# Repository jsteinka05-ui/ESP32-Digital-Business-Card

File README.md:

# ESP32 Digital Business Card

A standalone digital business card built around a **Seeed Studio XIAO ESP32-C3** and a **3.5-inch ILI9488 SPI TFT display**. This repository documents its hardware and a firmware rewrite in **C using ESP-IDF**.

The device is designed to display personal contact information and a LinkedIn QR code, with a single button for slide navigation, display recovery, and wake-up.

[Watch the device demonstration](docs/media/device-demo.mp4) — slide transitions, LCD power switching, and display recovery.

## Project Status

The custom PCB assembly, wiring, printed enclosure, and C firmware rewrite are complete. The ESP-IDF v6.1 firmware supports debounced button input, embedded slides, animated navigation, LCD recovery, and five-minute inactivity sleep with button wake.

Functional hardware checks and a clean-checkout build are complete. Recorded results include five startup draws at 238 ms each and twenty transitions averaging 2,604.75 ms, with unchanged sampled free heap. See the [validation record](docs/testing.md) for methods and limits. Current consumption and physical wake latency are outside this release's measurement scope.

Hardware design files and printable enclosure models are available under [hardware/](hardware/README.md).

## Features

- Business-card and LinkedIn QR-code slides.
- Standalone operation with images embedded in firmware; no network connection or SD card required.
- Animated transitions controlled by a physical button.
- Long-press recovery after the LCD is power-cycled independently of the microcontroller.

- Low-power idle after five minutes without button input.
- Button wake-up that restores the current slide without advancing it.

The current backlight is powered directly from the display supply. Automatic backlight shutdown would require a hardware change. Wi-Fi and Bluetooth Low Energy are future expansion options.

## Hardware and Design Choices

| Part | Purpose |
|---|---|
| Seeed Studio XIAO ESP32-C3 | Compact controller with flash storage, SPI, and room for wireless expansion |
| 3.5-inch ILI9488 SPI TFT | Color contact-information and QR-code display |
| Momentary pushbutton | Navigation, display recovery, and wake-up |
| LCD power switch | Controls LCD power independently of the microcontroller |

The ESP32-C3 can be considered overkill for displaying two images and reading a button. I chose it to leave room for future Wi-Fi and Bluetooth Low Energy functionality without replacing the controller.

Embedded images keep the initial storage design simple, while SPI limits the display wiring. The tradeoffs include flash usage, display-update bandwidth, and the need to rebuild firmware when artwork changes.

See the [design document](docs/design.md) for component rationale, wiring, memory calculations, and power-management considerations.

## Intended Controls

The firmware rewrite targets the following controls, including sleep and wake behavior:

| Input or condition | Intended behavior |
|---|---|
| Short press: less than 900 ms | Advance to the next slide upon release |
| Long press: at least 900 ms | Reinitialize the LCD and redraw the current slide upon release |
| Five minutes without button input | Enter a low-power idle state |
| Button press while idle | Wake and restore the current slide; consume the gesture without navigation |

The LCD switch leaves the ESP32-C3 running. Display recovery is needed because restoring LCD power does not automatically repeat the panel initialization sequence.

Button-only wake-up assumes the LCD supply switch remains on. If the LCD is manually switched off, restore its power before waking the device or requesting display recovery.

## Repository Layout

```text
firmware/                 ESP-IDF application and build configuration
    main/                 Application logic
    components/ili9488/   Display driver
    images/               Source artwork and display assets
    tools/                Image conversion utilities
hardware/                 Hardware documentation
    schematic/            KiCad project, PCB, schematic, and local libraries
    manufacturing/        Versioned Gerber and drill packages
    enclosure/            Printable STL models and enclosure notes
docs/                     Design decisions and testing documentation
.github/workflows/        Future automated build checks
```

## Development Setup

The intended development environment is:

- VS Code with ESP-IDF extension.
- ESP-IDF with the ESP32-C3 target and its toolchain.
- A USB data connection to the XIAO ESP32-C3.
- Python with Pillow for artwork conversion; the saved RGB assets allow firmware builds without Pillow.

Firmware development takes place under `firmware/`. The application includes debounced input, streamed image drawing, and slide navigation. The [progress log](docs/progress.md) distinguishes implemented features from verified hardware behavior.

## Roadmap

- [x] Establish repository structure and ignore rules.
- [x] Document the initial design.
- [x] Complete prototype wiring, custom PCB assembly, and printed enclosure.
- [x] Organize KiCad files, manufacturing exports, and enclosure models.
- [x] Implement startup logging and debounced button input.
- [x] Initialize the display and verify drawing, colors, and orientation.
- [x] Display embedded slides and implement navigation.
- [x] Add LCD recovery and animated transitions.
- [x] Implement inactivity sleep and button wake-up.
- [x] Verify sleep/wake on hardware.
- [x] Publish build instructions, test results, and a device demonstration.

## Documentation

- [Firmware rewrite design](docs/design.md): architecture, hardware selection, interaction rules, and validation plan.
- [Firmware validation](docs/testing.md): build checks, simulated button tests, and hardware results.
- [Firmware development plan](docs/firmware-plan.md): implementation stages and completion criteria.
- [Hardware](hardware/README.md): KiCad project, parts inventory, and manufacturing revisions.
- [Enclosure](hardware/enclosure/README.md): top case, bottom case, and button models.
- [Progress and commit log](docs/progress.md): milestones, checks, and commit references.

## License

Third-party library sources and licensing are listed in the [library documentation](hardware/schematic/libraries/README.md), with the upstream license included alongside its files.

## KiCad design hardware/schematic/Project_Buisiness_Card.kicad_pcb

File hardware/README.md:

# Hardware

The digital business card uses a custom PCB and a three-part printed enclosure. PCB assembly, wiring, and the physical prototype are complete.

## Directory Layout

```text
schematic/
    Project_Buisiness_Card.kicad_pro  KiCad project
    Project_Buisiness_Card.kicad_sch  Circuit schematic
    Project_Buisiness_Card.kicad_pcb  PCB layout
    fp-lib-table                    Footprint libraries
    sym-lib-table                   Symbol libraries
    Library.pretty/                 Custom footprint library
    libraries/                      XIAO symbols and footprints
manufacturing/
    Buisiness_Card_Gerbers_1.2.zip
    Buisiness_Card_Gerbers_1.3.zip
    Project_Buisiness_Gerbers_1.4.zip
enclosure/
    Top_Case.stl
    Bottom_Case.stl
    Button (1).stl
```

The schematic, PCB, and project settings share a directory and base name so KiCad can associate them as one project.

## KiCad Project

Open [Project_Buisiness_Card.kicad_pro](schematic/Project_Buisiness_Card.kicad_pro) in KiCad 9.0. The XIAO libraries are stored locally and use project-relative paths.

The PCB uses a custom through-hole XIAO footprint. The original surface-mount footprint is available under a separate library name. The active assignment uses the through-hole version.

[Library documentation](schematic/libraries/README.md) describes the footprint variants, project assignments, and upstream sources.

## Fabricated PCB

Bare revision 1.4 PCB before component installation. The component side shows the XIAO footprint, display header, passive-component positions, and button and power-switch connections.

| Component side | Reverse side |
|---|---|
|  |  |

## Manufacturing Files

Version **1.4** is the current hardware revision. Versions 1.2 and 1.3 are retained as earlier exports. Each archive contains Gerber layers and plated/non-plated drill files.

## Enclosure

The enclosure consists of a [top case](enclosure/Top_Case.stl), [bottom case](enclosure/Bottom_Case.stl), and [button](<enclosure/Button (1).stl>).

See the [enclosure documentation](enclosure/README.md) for the printable models.

## Components

| Component | Quantity | Function |
|---|---:|---|
| Seeed Studio XIAO ESP32-C3 | 1 | Display control and button processing |
| 3.5-inch ILI9488 SPI TFT | 1 | Contact-information and QR-code display |
| SPST slide switch | 1 | LCD power control |
| Momentary pushbutton | 1 | Slide navigation and display recovery |
| 1 × 14 header, 2.54 mm pitch | 1 | LCD connection |

## Schematic Values and Footprint Assignments

These entries describe the KiCad design. Switch model names identify the assigned footprints.

| Reference | Schematic value | Footprint |
|---|---|---|
| U1 | XIAO ESP32C3 | Project-specific through-hole XIAO footprint |
| SW1 | SW_SPST | Wuerth WS-SLTV slide-switch footprint |
| SW2 | SW_Push | APEM MJTP1243 pushbutton footprint |
| J_LCD1 | Conn_01x14 | 1 × 14 pin header, 2.54 mm pitch |
| J_BAT1 | Two-pin connector | — |
| C1, C3 | 0.1 µF | Radial capacitor, 5 mm lead spacing |
| C2, C4 | 10 µF | Radial capacitor, 5 mm lead spacing |
| R4, R6 | `46` | Axial resistor, 7.62 mm lead spacing |

The [design specification](../docs/design.md#existing-prototype-wiring) contains the GPIO mapping and LCD power behavior.

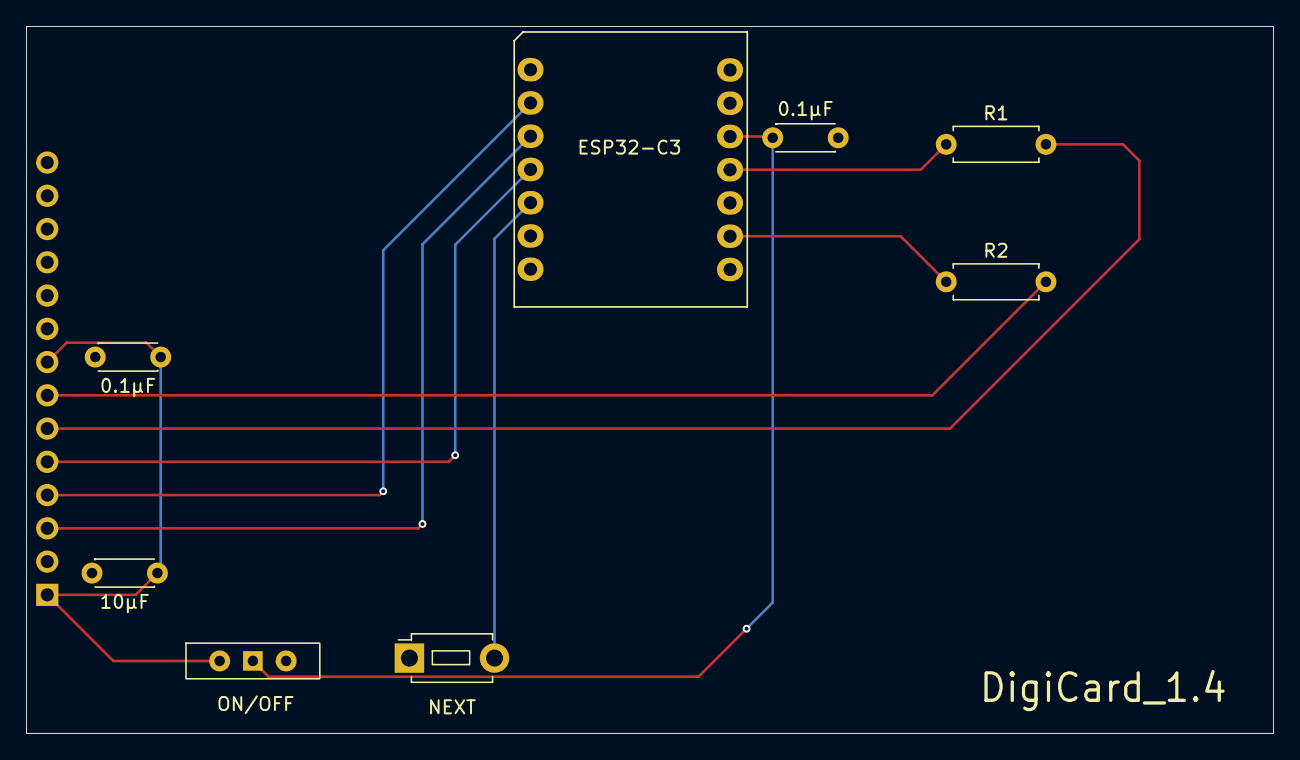
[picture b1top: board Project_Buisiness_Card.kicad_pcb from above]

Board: 2 copper layers, 95.2 x 54.0 mm, 9 parts (1 on the bottom side), 11 nets.

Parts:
0.1μF, 0.1μF#2: 0.1u; C_Disc_D4.3mm_W1.9mm_P5.00mm
10μF: 10u; C_Disc_D4.3mm_W1.9mm_P5.00mm
J_LCD1: Conn_01x14; PinHeader_1x14_P2.54mm_Vertical
NEXT: SW_Push; SW_PUSH_1P1T_6x3.5mm_H4.3_APEM_MJTP1243
R1, R2: 46; R_Axial_DIN0207_L6.3mm_D2.5mm_P7.62mm_Horizontal
SW1: SW_SPST; SW_Slide-03_Wuerth-WS-SLTV_10x2.5x6.4_P2.54mm
U1: XIAO ESP32C3; MOUDLE14P-SMD-2.54-21X17.8MM

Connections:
GND: 0.1μF.2, 0.1μF#2.2, 10μF.2, J_LCD1.2, NEXT.1, U1.13 (GND)
unnamed: 0.1μF.1, 10μF.1, J_LCD1.1, J_LCD1.8, SW1.2 (B)
unnamed: J_LCD1.3, U1.3 (D2)
unnamed: J_LCD1.4, U1.2 (D1)
unnamed: J_LCD1.5, U1.4 (D3)
unnamed: J_LCD1.6, R1.2
unnamed: J_LCD1.7, R2.2
unnamed: 0.1μF#2.1, SW1.1 (A), U1.12 (VCC_3V3)
unnamed: NEXT.2, U1.5 (D4)
unnamed: R2.1, U1.9 (D8)
unnamed: R1.1, U1.11 (D10)
